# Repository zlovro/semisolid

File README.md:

# semisolid
Audio power amplifier with a 12AX7 vacuum tube preamp and a solid state Class AB bridge tied load output.

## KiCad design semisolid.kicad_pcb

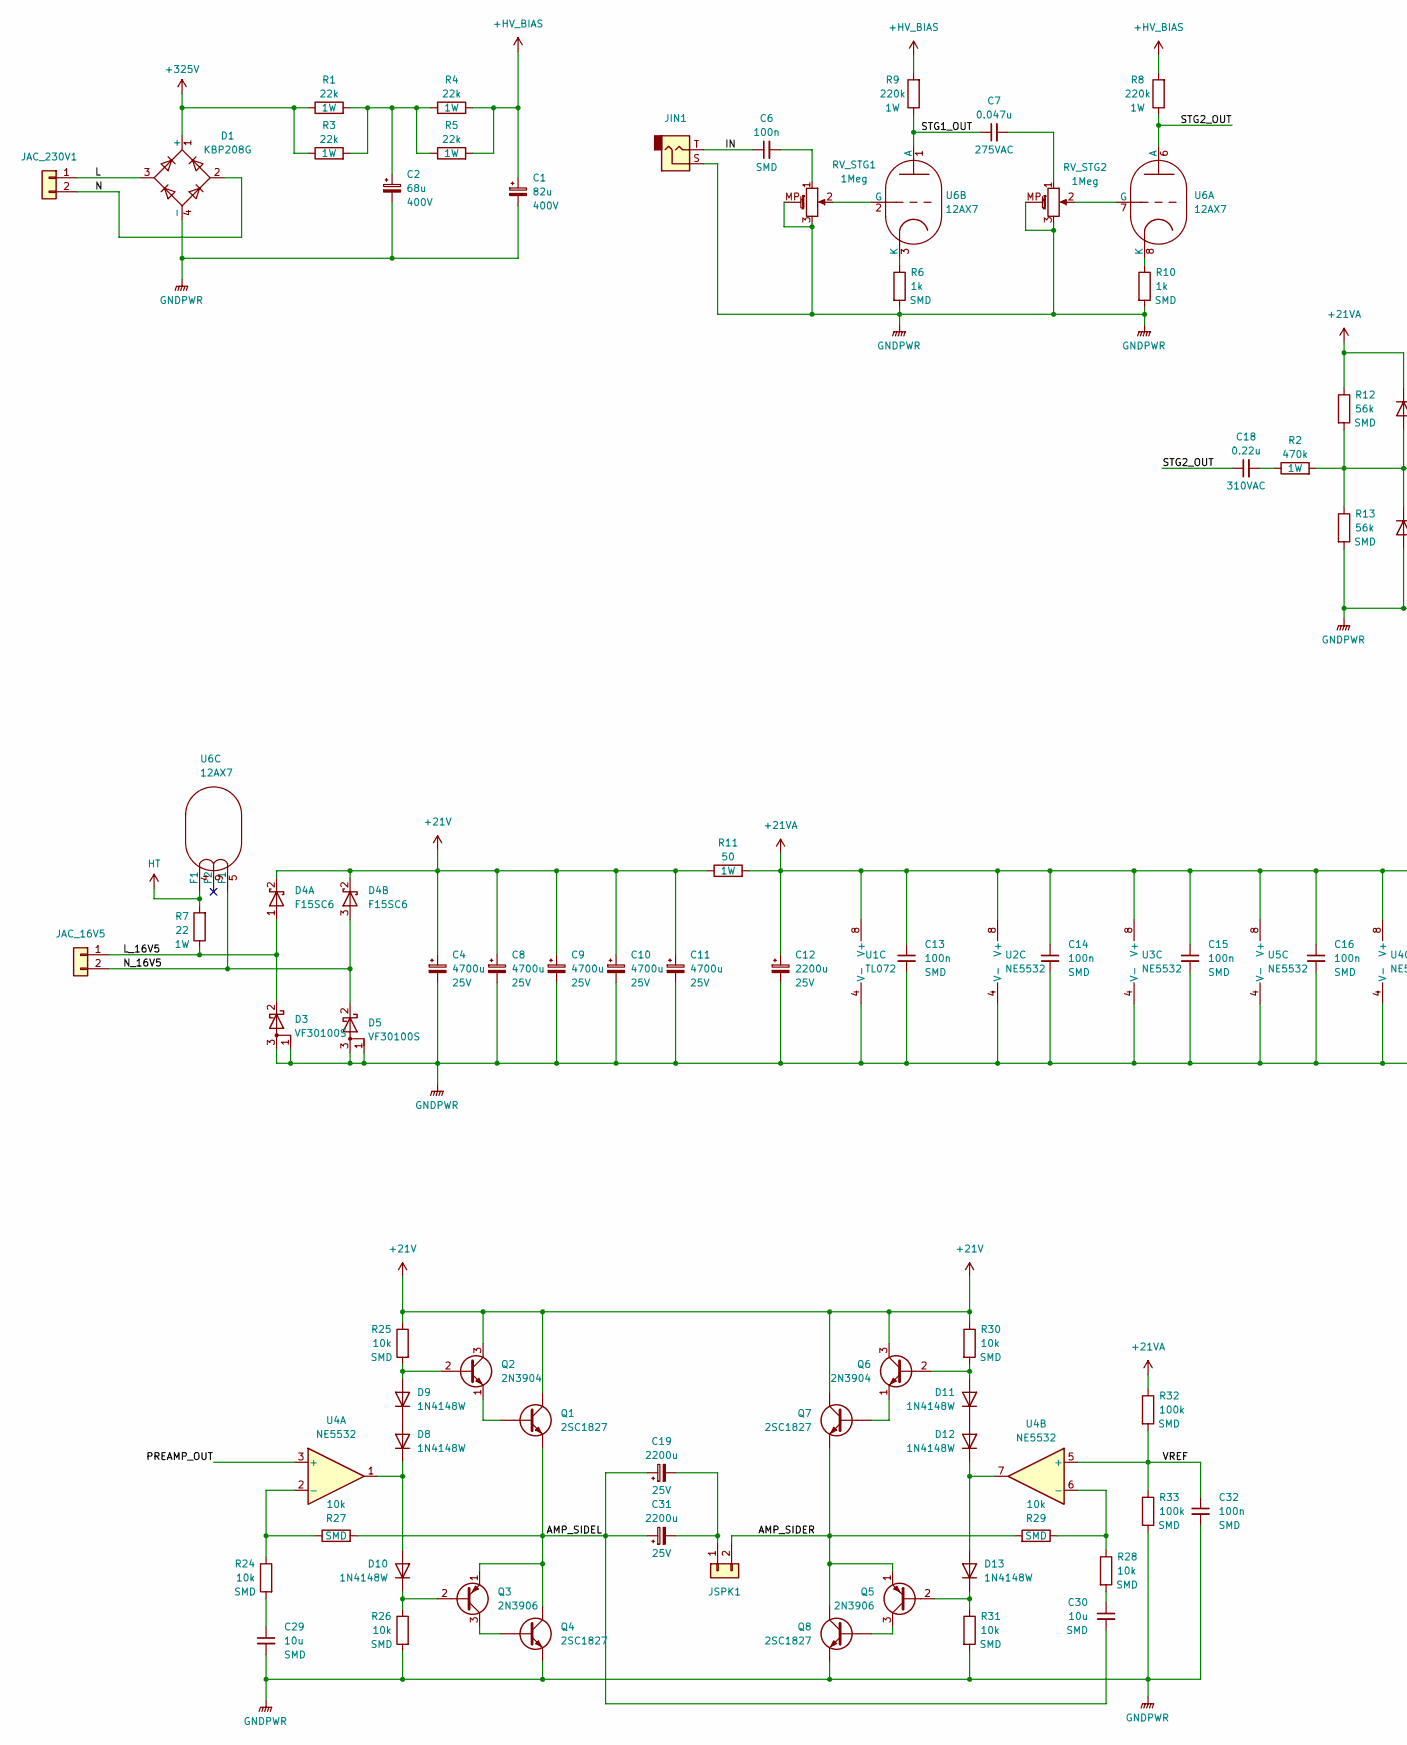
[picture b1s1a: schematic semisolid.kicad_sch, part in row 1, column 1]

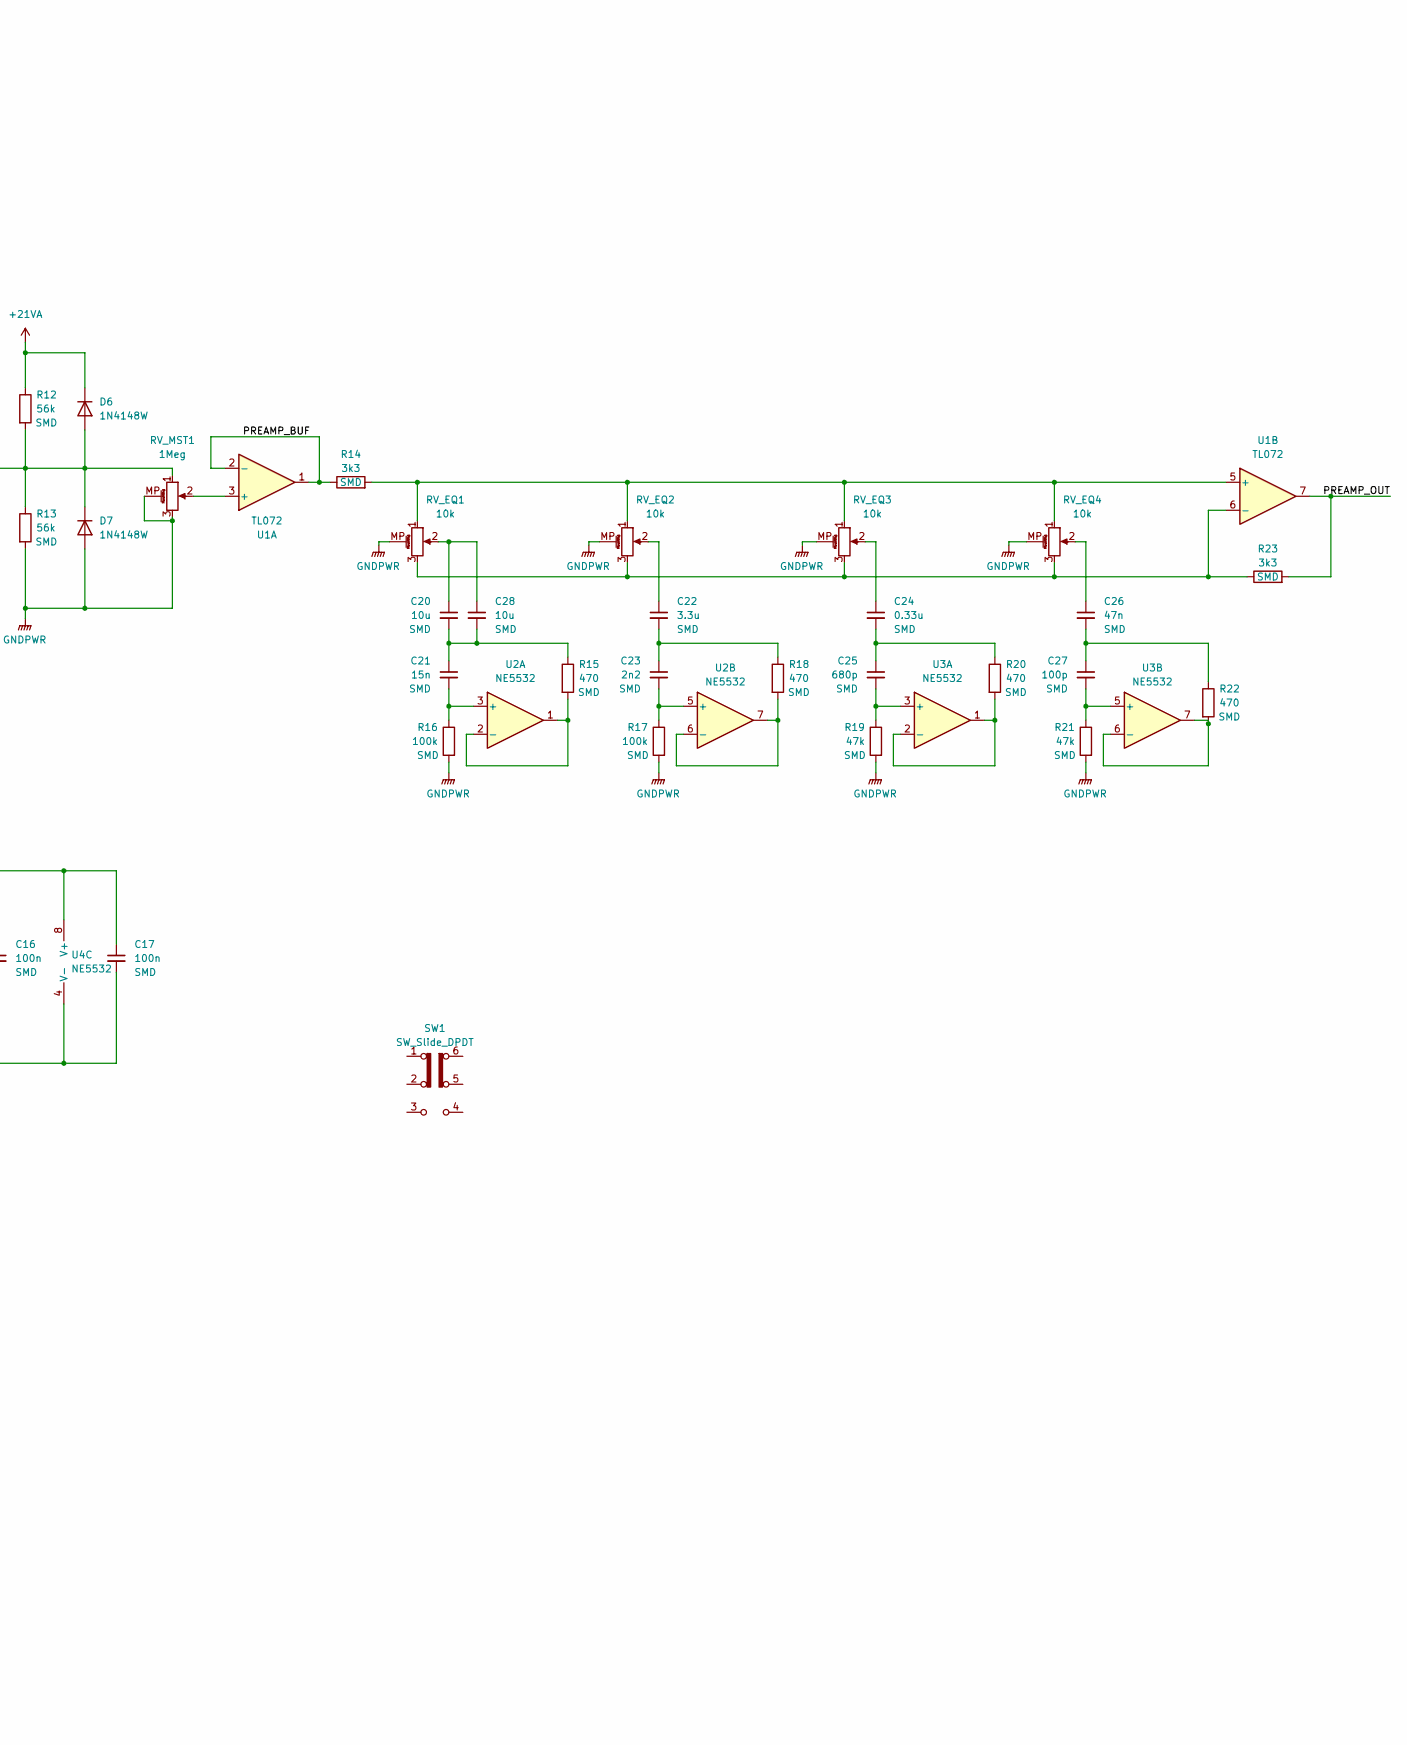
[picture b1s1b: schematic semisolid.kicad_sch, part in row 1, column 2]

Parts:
C1: 82u; CP_Radial_D18.0mm_P7.50mm; Voltage 400V
C2: 68u; CP_Radial_D18.0mm_P7.50mm; Voltage 400V
C4, C8, C9, C10, C11: 4700u; CP_Radial_D16.0mm_P7.50mm; Voltage 25V
C6, C13, C14, C15, C16, C17, C32: 100n; C_1206_3216Metric_Pad1.33x1.80mm_HandSolder
C7: 0.047u; C_Rect_L13.5mm_W5.0mm_P10.00mm_FKS3_FKP3_MKS4
C12: 2200u; CP_Radial_D18.0mm_P7.50mm; Voltage 25V
C18: 0.22u; C_Rect_L13.5mm_W5.0mm_P10.00mm_FKS3_FKP3_MKS4
C19, C31: 2200u; CP_Radial_D12.5mm_P5.00mm; Voltage 25V
C20, C28, C29, C30: 10u; C_1206_3216Metric_Pad1.33x1.80mm_HandSolder
C21: 15n; C_1206_3216Metric_Pad1.33x1.80mm_HandSolder
C22: 3.3u; C_1206_3216Metric_Pad1.33x1.80mm_HandSolder
C23: 2n2; C_1206_3216Metric_Pad1.33x1.80mm_HandSolder
C24: 0.33u; C_1206_3216Metric_Pad1.33x1.80mm_HandSolder
C25: 680p; C_1206_3216Metric_Pad1.33x1.80mm_HandSolder
C26: 47n; C_1206_3216Metric_Pad1.33x1.80mm_HandSolder
C27: 100p; C_1206_3216Metric_Pad1.33x1.80mm_HandSolder
D1: KBP208G
D3, D5: VF30100S; TO-220-3_Vertical
D4: F15SC6; TO-220-3_Vertical
D6, D7, D8, D9, D10, D11, D12, D13: 1N4148W; D_SOD-123
JAC_16V5, JAC_230V1: Conn_01x02; SolderWire-1sqmm_1x02_P7.8mm_D1.4mm_OD3.9mm
JIN1: NJ2FD-V; 6.35 horizontalni 4pin samesky TS NC
JSPK1: Conn_01x02; SolderWire-1sqmm_1x02_P7.8mm_D1.4mm_OD3.9mm
Q1, Q4, Q7, Q8: 2SC1827
Q2, Q6: 2N3904; TO-92L_Wide
Q3, Q5: 2N3906; TO-92L_Wide
R1, R3, R4, R5: 22k; R_Axial_DIN0411_L9.9mm_D3.6mm_P12.70mm_Horizontal
R2: 470k; R_Axial_DIN0411_L9.9mm_D3.6mm_P12.70mm_Horizontal
R6, R10: 1k; R_1206_3216Metric_Pad1.30x1.75mm_HandSolder
R7: 22; R_Axial_DIN0411_L9.9mm_D3.6mm_P12.70mm_Horizontal
R8, R9: 220k; R_Axial_DIN0411_L9.9mm_D3.6mm_P12.70mm_Horizontal
R11: 50; R_Axial_DIN0411_L9.9mm_D3.6mm_P12.70mm_Horizontal
R12, R13: 56k; R_1206_3216Metric_Pad1.30x1.75mm_HandSolder
R14, R23: 3k3; R_1206_3216Metric_Pad1.30x1.75mm_HandSolder
R15, R18, R20, R22: 470; R_1206_3216Metric_Pad1.30x1.75mm_HandSolder
R16, R17, R32, R33: 100k; R_1206_3216Metric_Pad1.30x1.75mm_HandSolder
R19, R21: 47k; R_1206_3216Metric_Pad1.30x1.75mm_HandSolder
R24, R25, R26, R27, R28, R29, R30, R31: 10k; R_1206_3216Metric_Pad1.30x1.75mm_HandSolder
RV_EQ1, RV_EQ2, RV_EQ3, RV_EQ4: 10k; pot vertikalni 5 pin
RV_MST1: 1Meg; pot vertikalni 5 pin
RV_STG1, RV_STG2: 1Meg; pot vertikalni 5 pin
SW1: SW_Slide_DPDT; DPDT_Rocker
U1: TL072; DIP-8_W7.62mm_Socket_LongPads
U2, U3, U4, U5: NE5532; DIP-8_W7.62mm_Socket_LongPads
U6: 12AX7; Valve_B9A

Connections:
+21V: C4.1, C8.1, C9.1, C10.1, C11.1, D4.2 (K), Q1.C, Q2.3 (C), Q6.3 (C), Q7.C, R11.1, R25.1, R30.1
+21VA: C12.1, C13.1, C14.1, C15.1, C16.1, C17.1, D6.1 (K), R11.2, R12.1, R32.1, U1.8 (V+), U2.8 (V+), U3.8 (V+), U4.8 (V+), U5.8 (V+)
+325V: D1.1 (+), R1.1, R3.1
+HV_BIAS: C1.1, R4.2, R5.2, R8.2, R9.2
/AMP_SIDEL: C19.1, C30.2, C31.1, Q1.E, Q3.1 (E), Q4.C, R27.2
/AMP_SIDER: JSPK1.2, Q5.1 (E), Q7.E, Q8.C, R29.2
/IN: C6.1, JIN1.T
/L: D1.3, JAC_230V1.1
/L_16V5: D3.2 (K), D4.1 (A), JAC_16V5.1, R7.1
/N: D1.2, JAC_230V1.2
/N_16V5: D4.3 (A), D5.2 (K), JAC_16V5.2, U6.5 (F1)
/PREAMP_BUF: R14.1, U1.1, U1.2 (-)
/PREAMP_OUT: R23.2, U1.7, U4.3 (+)
/STG1_OUT: C7.1, R9.1, U6.1 (A)
/STG2_OUT: C18.1, R8.1, U6.6 (A)
/VREF: C32.1, R32.2, R33.1, U4.5 (+)
GNDPWR: C1.2, C2.2, C4.2, C8.2, C9.2, C10.2, C11.2, C12.2, C13.2, C14.2, C15.2, C16.2, C17.2, C29.2, C32.2, D1.4 (-), D3.1 (A), D3.3 (A), D5.1 (A), D5.3 (A), D7.2 (A), JIN1.S, Q4.E, Q8.E, R6.2, R10.2, R13.2, R16.2, R17.2, R19.2, R21.2, R26.2, R31.2, R33.2, RV_EQ1.MP (MountPin), RV_EQ2.MP (MountPin), RV_EQ3.MP (MountPin), RV_EQ4.MP (MountPin), RV_MST1.3, RV_MST1.MP (MountPin), RV_STG1.3, RV_STG1.MP (MountPin), RV_STG2.3, RV_STG2.MP (MountPin), U1.4 (V-), U2.4 (V-), U3.4 (V-), U4.4 (V-), U5.4 (V-)
HT: R7.2, U6.4 (F1)
unnamed: C2.1, R1.2, R3.2, R4.1, R5.1
unnamed: C6.2, RV_STG1.1
unnamed: C7.2, RV_STG2.1
unnamed: C18.2, R2.1
unnamed: C20.1, C28.1, RV_EQ1.2
unnamed: C20.2, C21.1, C28.2, R15.1
unnamed: C22.1, RV_EQ2.2
unnamed: C22.2, C23.1, R18.1
unnamed: C24.1, RV_EQ3.2
unnamed: C24.2, C25.1, R20.1
unnamed: C26.1, RV_EQ4.2
unnamed: C26.2, C27.1, R22.1
unnamed: C29.1, R24.2
unnamed: C30.1, R28.2
unnamed: D6.2 (A), D7.1 (K), R2.2, R12.2, R13.1, RV_MST1.1
unnamed: D8.2 (A), D9.1 (K)
unnamed: D9.2 (A), Q2.2 (B), R25.2
unnamed: D8.1 (K), D10.2 (A), U4.1
unnamed: D10.1 (K), Q3.2 (B), R26.1
unnamed: D11.2 (A), Q6.2 (B), R30.2
unnamed: D11.1 (K), D12.2 (A)
unnamed: D12.1 (K), D13.2 (A), U4.7
unnamed: D13.1 (K), Q5.2 (B), R31.1
unnamed: C19.2, C31.2, JSPK1.1
unnamed: Q1.B, Q2.1 (E)
unnamed: Q3.3 (C), Q4.B
unnamed: Q5.3 (C), Q8.B
unnamed: Q6.1 (E), Q7.B
unnamed: RV_MST1.2, U1.3 (+)
unnamed: R14.2, RV_EQ1.1, RV_EQ2.1, RV_EQ3.1, RV_EQ4.1, U1.5 (+)
unnamed: R23.1, RV_EQ1.3, RV_EQ2.3, RV_EQ3.3, RV_EQ4.3, U1.6 (-)
unnamed: C21.2, R16.1, U2.3 (+)
unnamed: R15.2, U2.1, U2.2 (-)
unnamed: C23.2, R17.1, U2.5 (+)
unnamed: R18.2, U2.6 (-), U2.7
unnamed: C25.2, R19.1, U3.3 (+)
unnamed: R20.2, U3.1, U3.2 (-)
unnamed: C27.2, R21.1, U3.5 (+)
unnamed: R22.2, U3.6 (-), U3.7
unnamed: R24.1, R27.1, U4.2 (-)
unnamed: R28.1, R29.1, U4.6 (-)
unnamed: RV_STG2.2, U6.7 (G)
unnamed: R10.1, U6.8 (K)
unnamed: RV_STG1.2, U6.2 (G)
unnamed: R6.1, U6.3 (K)

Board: 2 copper layers, 96 parts (0 on the bottom side), 59 nets, no tracks yet.
